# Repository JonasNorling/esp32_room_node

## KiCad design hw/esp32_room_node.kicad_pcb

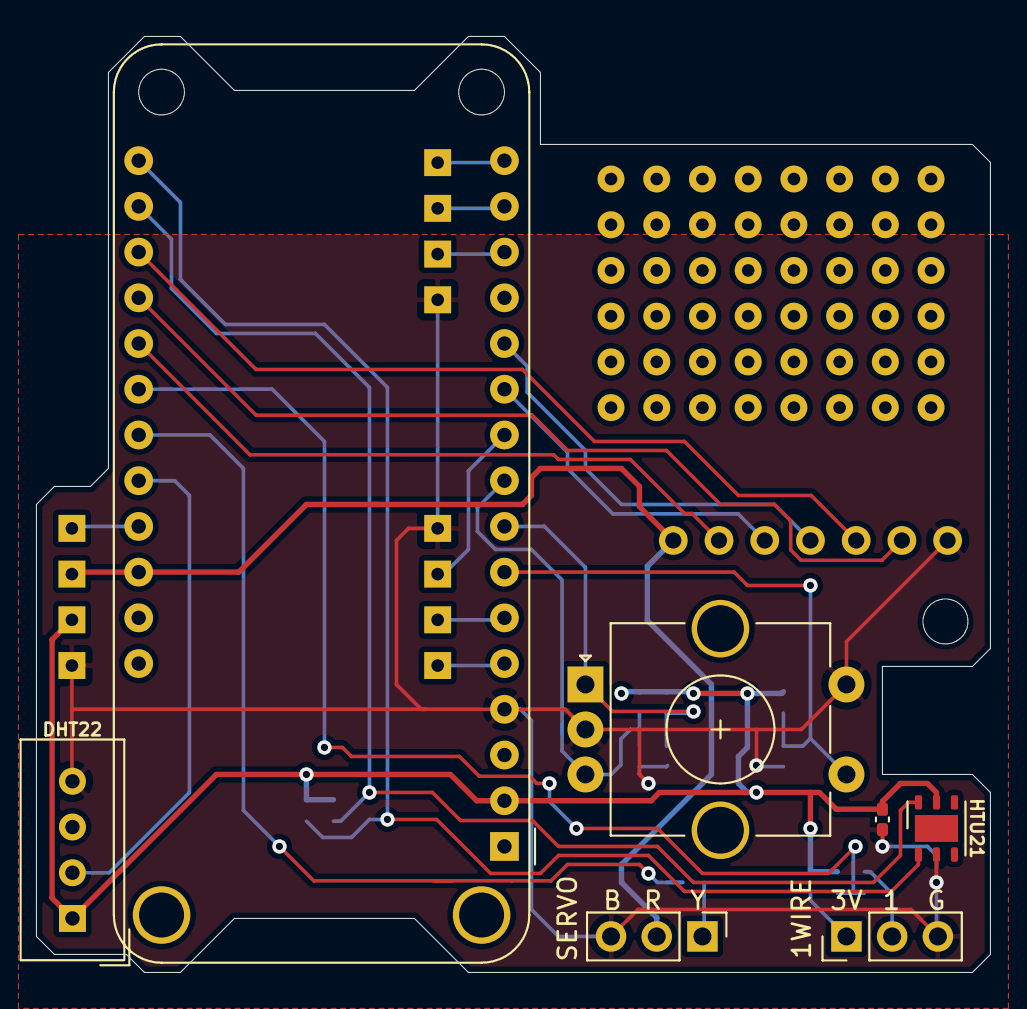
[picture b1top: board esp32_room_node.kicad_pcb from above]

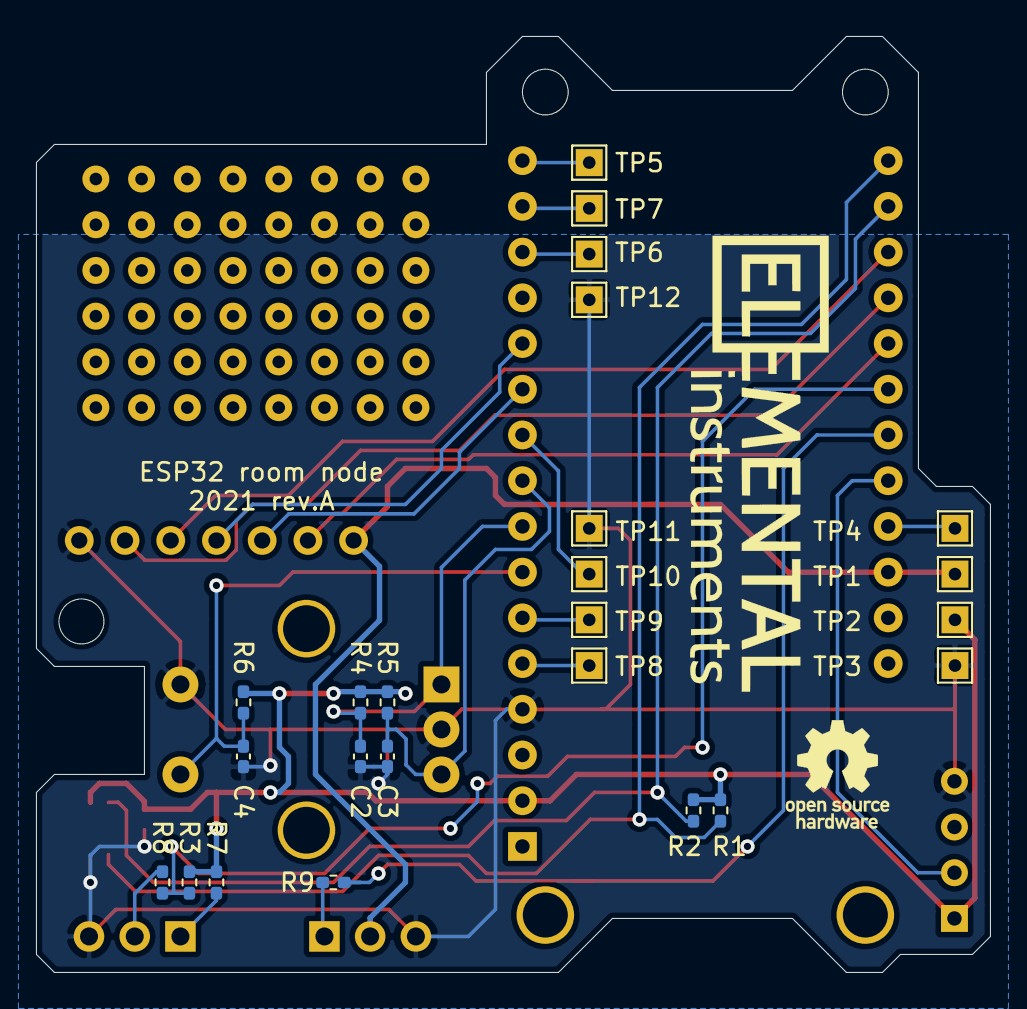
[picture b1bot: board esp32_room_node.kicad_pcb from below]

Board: 2 copper layers, 53.0 x 52.0 mm, 37 parts (26 on the bottom side), 26 nets.

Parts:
A1: Adafruit_Feather_HUZZAH32_ESP32; Adafruit_Feather_WithMountingHoles
C1: 100n; C_0402_1005Metric_Pad0.74x0.62mm_HandSolder
C2, C3, C4: DNP; C_0402_1005Metric_Pad0.74x0.62mm_HandSolder
DISP1: SPI LCD; PIM436
H1: MountingHole; MountingHole_2.5mm
J1, J2: Conn_01x03; PinHeader_1x03_P2.54mm_Vertical
LOGO1: Logo_Open_Hardware_Small; OSHW-Logo_5.7x6mm_SilkScreen
LOGO2: Logo_Open_Hardware_Small; elemental-4mm-mask
LOGO3: Logo_Open_Hardware_Small; elemental-25.4mm
PROTOAREA1: Logo_Open_Hardware_Small; protoarea
R1, R2, R4, R5, R6: R; R_0402_1005Metric_Pad0.72x0.64mm_HandSolder
R3: 4k7; R_0402_1005Metric_Pad0.72x0.64mm_HandSolder
R7, R8, R9: 10; R_0402_1005Metric_Pad0.72x0.64mm_HandSolder
SW1: Rotary_Encoder_Switch; RotaryEncoder_Alps_EC11E-Switch_Vertical_H20mm_CircularMoun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
TP1, TP2, TP3, TP4, TP5, TP6, TP7, TP8, TP9, TP10, TP11, TP12: TestPoint; TestPoint_THTPad_1.5x1.5mm_Drill0.7mm
U1: DHT11; Aosong_DHT11_5.5x12.0_P2.54mm
U2: HTU21; DFN-6-1EP_3x3mm_P1mm_EP1.5x2.4mm

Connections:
+3V3: A1.2, C1.1, R1.1, R2.1, R3.1, R4.1, R5.1, R6.1, R7.2, TP2.1, U1.1, U2.5
+5V: A1.26, DISP1.1, J2.2, TP1.1
/ENC_A: A1.8, C2.1, R4.2, SW1.A
/ENC_B: A1.9, C3.1, R5.2, SW1.B
/ENC_BTN: A1.7, C4.1, R6.2, SW1.S1
/LCD_BL: A1.20, DISP1.6
/LCD_CS: A1.21, DISP1.2
/LCD_DC: A1.19, DISP1.5
/LCD_MOSI: A1.12, DISP1.4
/LCD_SCK: A1.11, DISP1.3
/ONEWIRE: A1.22, R3.2, R8.2
/SCL: A1.18, R2.2, U2.6
/SDA: A1.17, R1.2, U2.1
/SENS_DATA: A1.24, U1.2
/SERVO: A1.23, R9.2
GND: A1.4, C1.2, C2.2, C3.2, C4.2, DISP1.7, J1.3, J2.3, SW1.C, SW1.S2, TP3.1, TP11.1, TP12.1, U1.4, U2.2
unnamed: A1.5, TP8.1
unnamed: A1.6, TP9.1
unnamed: A1.10, TP10.1
unnamed: A1.14, TP6.1
unnamed: A1.15, TP7.1
unnamed: A1.16, TP5.1
unnamed: A1.25, TP4.1
unnamed: J1.1, R7.1
unnamed: J1.2, R8.1
unnamed: J2.1, R9.1

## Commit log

2021-07-25 Blink red LED
2021-07-29 Read RHT03 sensor
2021-08-10 Enable BMP280 sensor on I2C
    It doesn't work. I think Zephyr + ESP32 is flaky with I2C; there are
    missing stop conditions and clocks. i2c_write_read() had to be patched
    to get anything working.
2021-08-10 BMP280 sensor on SPI
2021-08-11 WIP: Drive LCD
2021-08-11 Shit is still weird, but it 'works'
2021-08-12 WIP: Display grid
2021-08-12 Changing display
2021-08-12 Enable LVGL
2021-08-12 Display temp and RH
2021-08-12 Disable WiFi
2021-08-13 WIP PWM
2021-08-13 Working servo control
2021-08-13 Control servo, show one decimal
2021-08-15 Don't use immediate logging
2021-08-15 Read encoder
2021-08-15 Add display to schematic
2021-08-15 Footprint assignment
2021-08-15 Move fw into fw/
2021-08-15 Initial schematic
2021-08-15 Move encoder pinout
2021-08-15 Add encoder to schematic, outline
2021-08-15 Routed PCB
2021-08-15 Add prototype area
2021-08-15 Adjust silk
2021-08-15 GUI focus support
2021-08-20 Move GUI code to separate file
2021-08-20 Silly GUI work
2021-08-20 Use a Zephyr kernel timer for input polling
2021-08-21 Configuration storage
2021-08-21 Some servo config in GUI
2021-08-21 Config as floats
